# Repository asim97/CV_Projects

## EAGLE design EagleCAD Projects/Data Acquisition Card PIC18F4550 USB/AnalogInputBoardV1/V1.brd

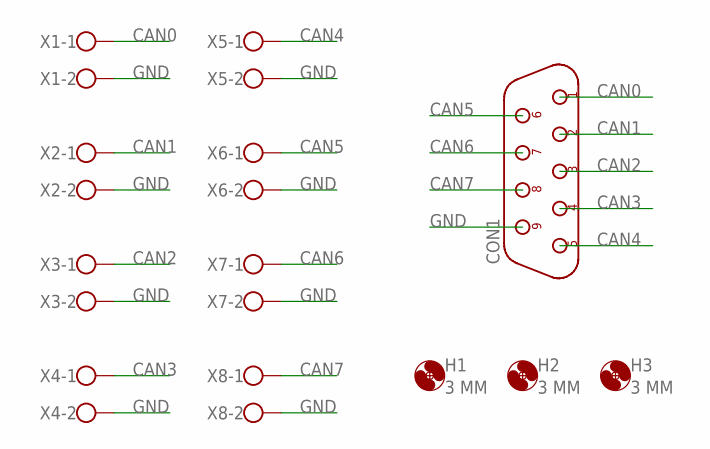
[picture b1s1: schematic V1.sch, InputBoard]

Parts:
CON1: DB9F/90; D-09F/90
H1, H2, H3: 3 MM; 3,0
X1, X2, X3, X4, X5, X6, X7, X8: W237-102

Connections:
CAN0: CON1.1, X1.1
CAN1: CON1.2, X2.1
CAN2: CON1.3, X3.1
CAN3: CON1.4, X4.1
CAN4: CON1.5, X5.1
CAN5: CON1.6, X6.1
CAN6: CON1.7, X7.1
CAN7: CON1.8, X8.1
GND: CON1.9, X1.2, X2.2, X3.2, X4.2, X5.2, X6.2, X7.2, X8.2

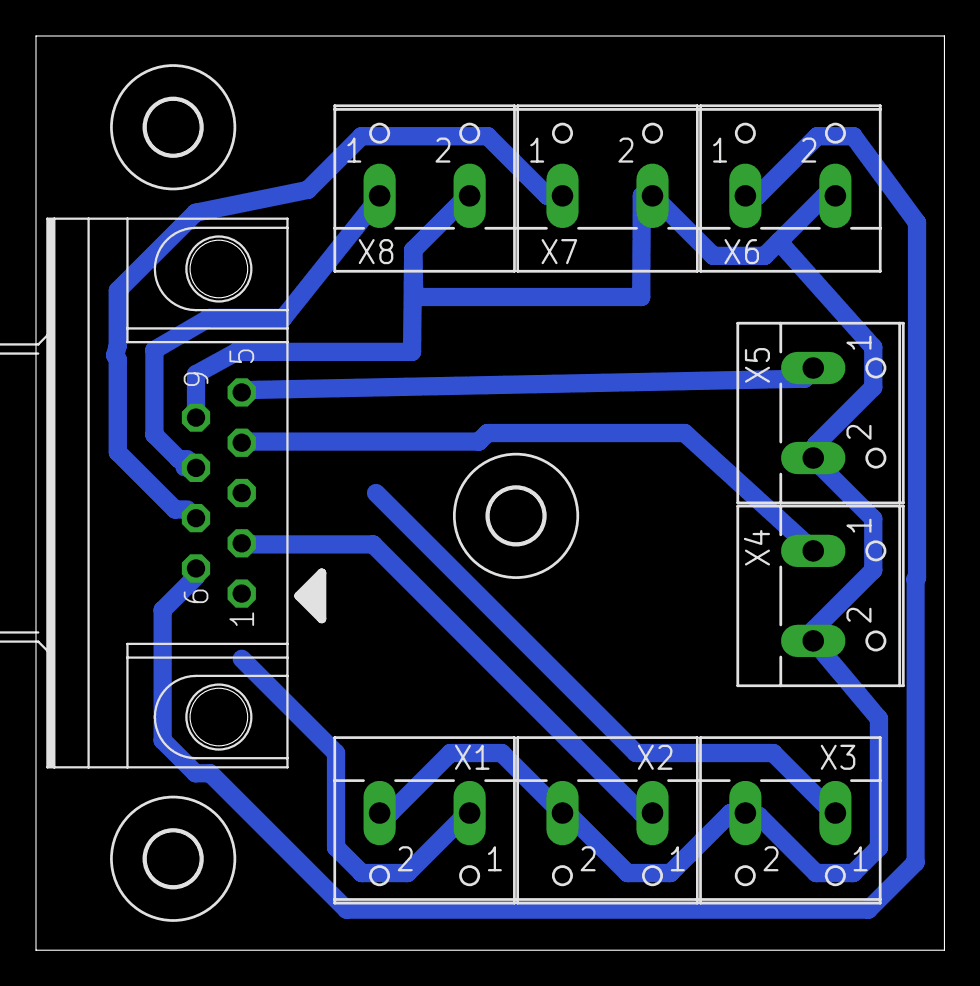
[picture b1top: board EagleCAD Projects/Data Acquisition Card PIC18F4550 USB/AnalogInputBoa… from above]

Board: 2 copper layers, 50.5 x 50.8 mm, 12 parts (0 on the bottom side), 9 nets.

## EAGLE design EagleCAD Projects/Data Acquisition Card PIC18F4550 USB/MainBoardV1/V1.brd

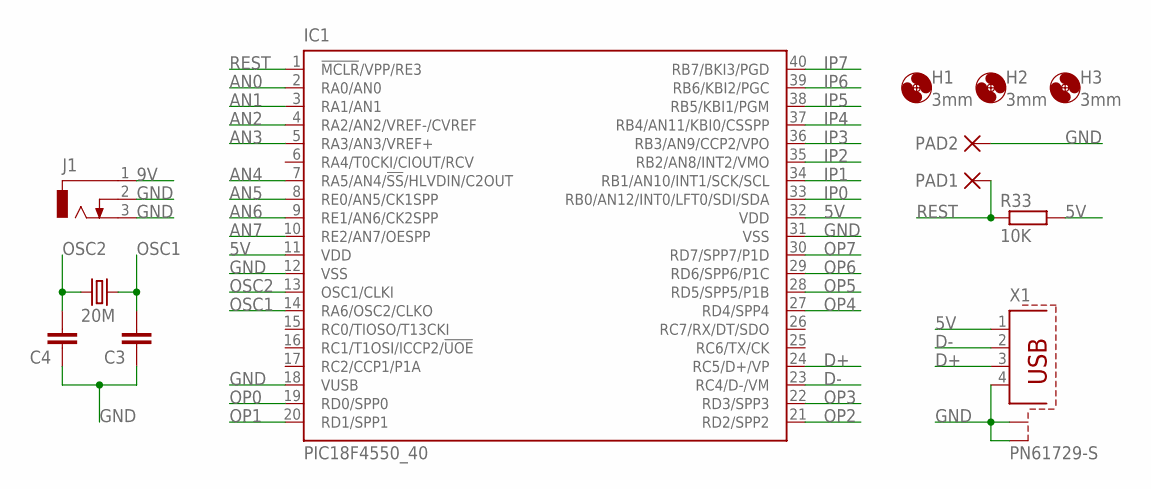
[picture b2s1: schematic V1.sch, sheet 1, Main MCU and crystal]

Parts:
20M: CRYSTALHC18U-V; HC18U-V
C3, C4: C5/2.5; C5B2.5
H1, H2, H3: 3mm; 3,0
IC1: PIC18F4550_40; DIL40
J1: DCJ0303
PAD1, PAD2: PAD-0320; 0320
R33: 10K; 0207/10
X1: PN61729-S

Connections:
5V: IC1.11 (VDD), IC1.32 (VDD), R33.2, X1.1; also elsewhere on the board
9V: J1.1; also elsewhere on the board
AN0: IC1.2 (RA0/AN0); also elsewhere on the board
AN1: IC1.3 (RA1/AN1); also elsewhere on the board
AN2: IC1.4 (RA2/AN2/VREF-/CVREF); also elsewhere on the board
AN3: IC1.5 (RA3/AN3/VREF+); also elsewhere on the board
AN4: IC1.7 (RA5/AN4/!SS!/HLVDIN/C2OUT); also elsewhere on the board
AN5: IC1.8 (RE0/AN5/CK1SPP); also elsewhere on the board
AN6: IC1.9 (RE1/AN6/CK2SPP); also elsewhere on the board
AN7: IC1.10 (RE2/AN7/OESPP); also elsewhere on the board
D+: IC1.24 (RC5/D+/VP), X1.3
D-: IC1.23 (RC4/D-/VM), X1.2
GND: C3.1, C4.1, IC1.12 (VSS), IC1.18 (VUSB), IC1.31 (VSS), J1.2, J1.3, PAD2.P$1, X1.4, X1.S1, X1.S2; also elsewhere on the board
IP0: IC1.33 (RB0/AN12/INT0/LFT0/SDI/SDA); also elsewhere on the board
IP1: IC1.34 (RB1/AN10/INT1/SCK/SCL); also elsewhere on the board
IP2: IC1.35 (RB2/AN8/INT2/VMO); also elsewhere on the board
IP3: IC1.36 (RB3/AN9/CCP2/VPO); also elsewhere on the board
IP4: IC1.37 (RB4/AN11/KBI0/CSSPP); also elsewhere on the board
IP5: IC1.38 (RB5/KBI1/PGM); also elsewhere on the board
IP6: IC1.39 (RB6/KBI2/PGC); also elsewhere on the board
IP7: IC1.40 (RB7/BKI3/PGD); also elsewhere on the board
OP0: IC1.19 (RD0/SPP0); also elsewhere on the board
OP1: IC1.20 (RD1/SPP1); also elsewhere on the board
OP2: IC1.21 (RD2/SPP2); also elsewhere on the board
OP3: IC1.22 (RD3/SPP3); also elsewhere on the board
OP4: IC1.27 (RD4/SPP4); also elsewhere on the board
OP5: IC1.28 (RD5/SPP5/P1B); also elsewhere on the board
OP6: IC1.29 (RD6/SPP6/P1C); also elsewhere on the board
OP7: IC1.30 (RD7/SPP7/P1D); also elsewhere on the board
OSC1: 20M.2, C3.2, IC1.14 (RA6/OSC2/CLKO)
OSC2: 20M.1, C4.2, IC1.13 (OSC1/CLKI)
REST: IC1.1 (!MCLR!/VPP/RE3), PAD1.P$1, R33.1

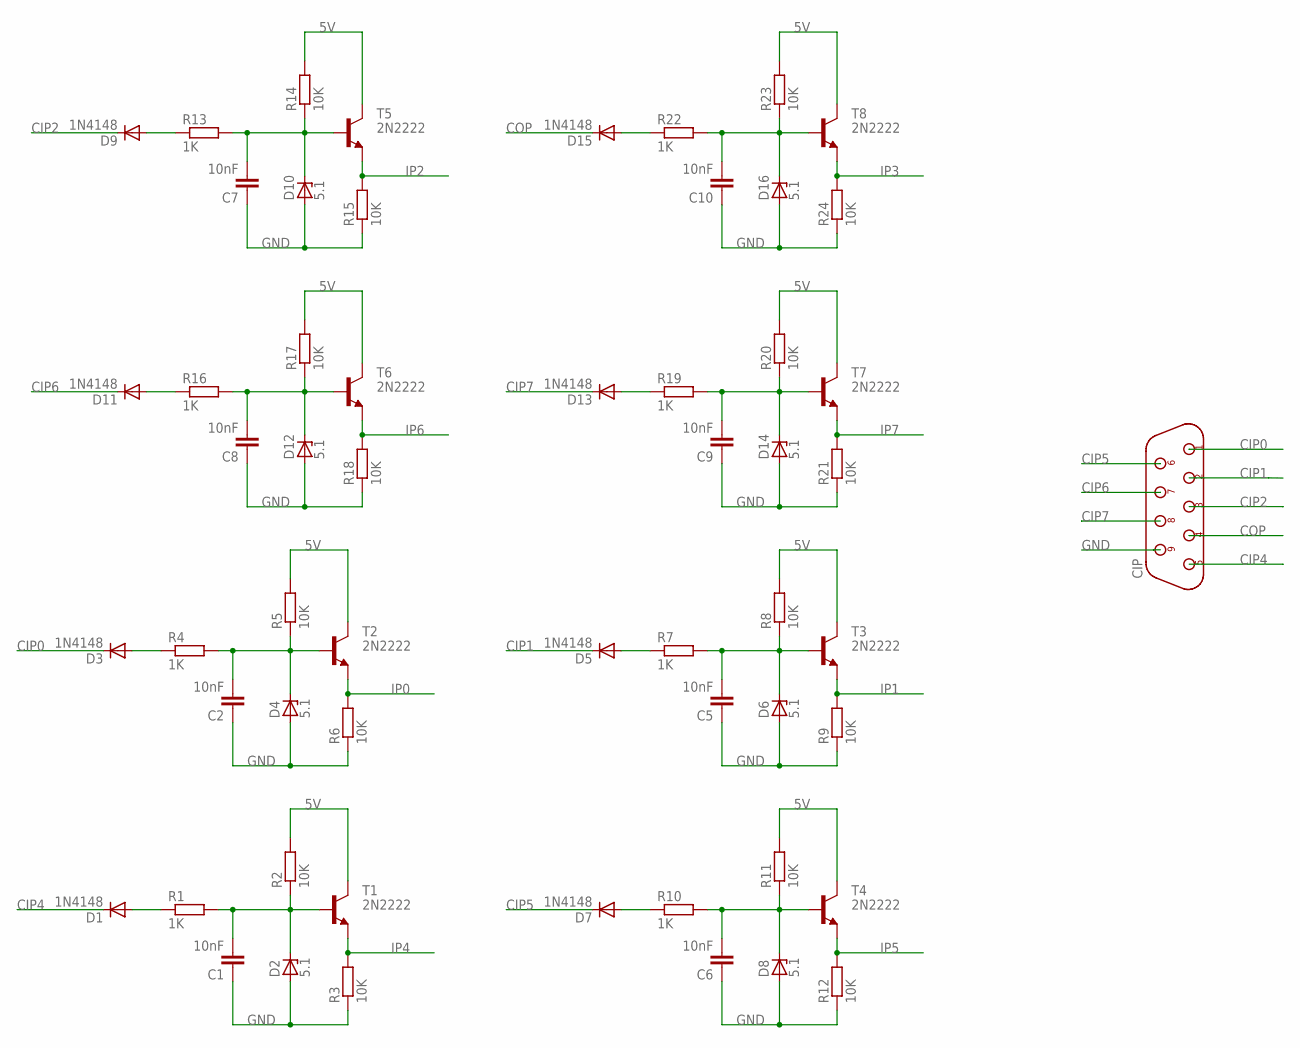
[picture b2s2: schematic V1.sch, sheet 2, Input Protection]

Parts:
C1, C2, C5, C6, C7, C8, C9, C10: 10nF; C5B2.5
CIP: DB9F/90; D-09F/90
D1, D3, D5, D7, D9, D11, D13, D15: 1N4148; DO35-10
D2, D4, D6, D8, D10, D12, D14, D16: 5.1; ZDIO-10
R1, R4, R7, R10, R13, R16, R19, R22: 1K; 0207/10
R2, R3, R5, R6, R8, R9, R11, R12, R14, R15, R17, R18, R20, R21, R23, R24: 10K; 0207/10
T1, T2, T3, T4, T5, T6, T7, T8: 2N2222; TO92-EBC-OVAL

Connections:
5V: R2.2, R5.2, R8.2, R11.2, R14.2, R17.2, R20.2, R23.2, T1.C, T2.C, T3.C, T4.C, T5.C, T6.C, T7.C, T8.C; also elsewhere on the board
CIP0: CIP.1, D3.C
CIP1: CIP.2, D5.C
CIP2: CIP.3, D9.C
CIP4: CIP.5, D1.C
CIP5: CIP.6, D7.C
CIP6: CIP.7, D11.C
CIP7: CIP.8, D13.C
COP: CIP.4, D15.C
GND: C1.1, C2.1, C5.1, C6.1, C7.1, C8.1, C9.1, C10.1, CIP.9, D2.A, D4.A, D6.A, D8.A, D10.A, D12.A, D14.A, D16.A, R3.1, R6.1, R9.1, R12.1, R15.1, R18.1, R21.1, R24.1; also elsewhere on the board
IP0: R6.2, T2.E; also elsewhere on the board
IP1: R9.2, T3.E; also elsewhere on the board
IP2: R15.2, T5.E; also elsewhere on the board
IP3: R24.2, T8.E; also elsewhere on the board
IP4: R3.2, T1.E; also elsewhere on the board
IP5: R12.2, T4.E; also elsewhere on the board
IP6: R18.2, T6.E; also elsewhere on the board
IP7: R21.2, T7.E; also elsewhere on the board
unnamed: D1.A, R1.1
unnamed: C1.2, D2.C, R1.2, R2.1, T1.B
unnamed: D3.A, R4.1
unnamed: C2.2, D4.C, R4.2, R5.1, T2.B
unnamed: D5.A, R7.1
unnamed: C5.2, D6.C, R7.2, R8.1, T3.B
unnamed: D7.A, R10.1
unnamed: C6.2, D8.C, R10.2, R11.1, T4.B
unnamed: D9.A, R13.1
unnamed: C7.2, D10.C, R13.2, R14.1, T5.B
unnamed: D11.A, R16.1
unnamed: C8.2, D12.C, R16.2, R17.1, T6.B
unnamed: D13.A, R19.1
unnamed: C9.2, D14.C, R19.2, R20.1, T7.B
unnamed: D15.A, R22.1
unnamed: C10.2, D16.C, R22.2, R23.1, T8.B

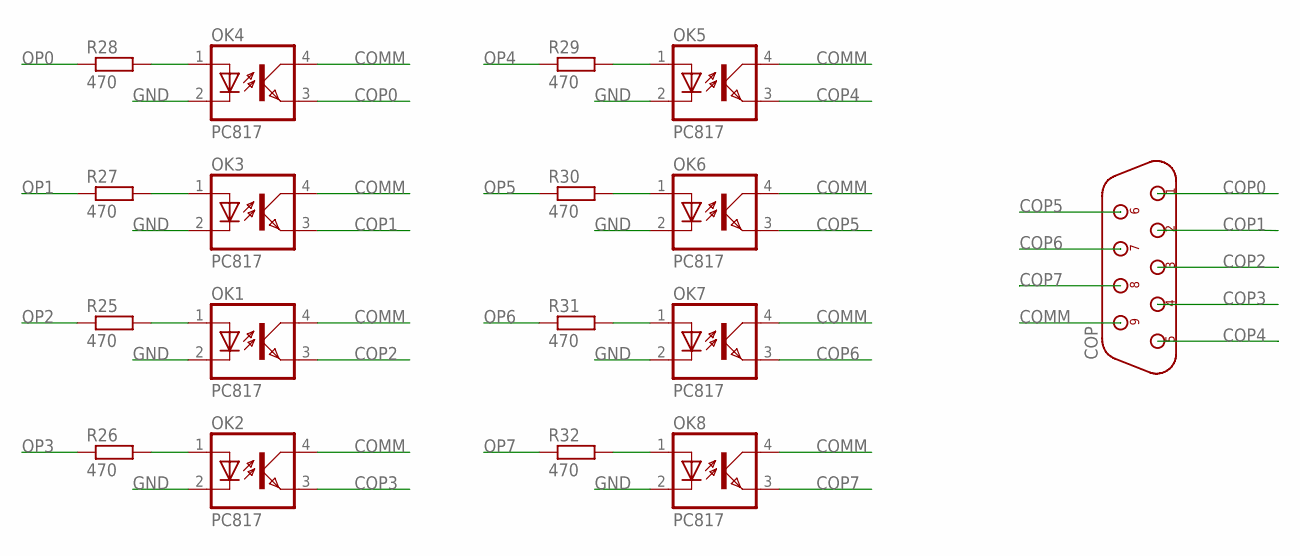
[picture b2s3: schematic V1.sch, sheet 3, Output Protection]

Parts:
COP: DB9F/90; D-09F/90
OK1, OK2, OK3, OK4, OK5, OK6, OK7, OK8: PC817; DIL04
R25, R26, R27, R28, R29, R30, R31, R32: 470; 0207/10

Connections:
COMM: COP.9, OK1.4 (COL), OK2.4 (COL), OK3.4 (COL), OK4.4 (COL), OK5.4 (COL), OK6.4 (COL), OK7.4 (COL), OK8.4 (COL)
COP0: COP.1, OK4.3 (EMIT)
COP1: COP.2, OK3.3 (EMIT)
COP2: COP.3, OK1.3 (EMIT)
COP3: COP.4, OK2.3 (EMIT)
COP4: COP.5, OK5.3 (EMIT)
COP5: COP.6, OK6.3 (EMIT)
COP6: COP.7, OK7.3 (EMIT)
COP7: COP.8, OK8.3 (EMIT)
GND: OK1.2 (C), OK2.2 (C), OK3.2 (C), OK4.2 (C), OK5.2 (C), OK6.2 (C), OK7.2 (C), OK8.2 (C); also elsewhere on the board
unnamed: OK1.1 (A), R25.2
unnamed: OK2.1 (A), R26.2
unnamed: OK3.1 (A), R27.2
unnamed: OK4.1 (A), R28.2
unnamed: OK5.1 (A), R29.2
unnamed: OK6.1 (A), R30.2
unnamed: OK7.1 (A), R31.2
unnamed: OK8.1 (A), R32.2
OP0: R28.1; also elsewhere on the board
OP1: R27.1; also elsewhere on the board
OP2: R25.1; also elsewhere on the board
OP3: R26.1; also elsewhere on the board
OP4: R29.1; also elsewhere on the board
OP5: R30.1; also elsewhere on the board
OP6: R31.1; also elsewhere on the board
OP7: R32.1; also elsewhere on the board

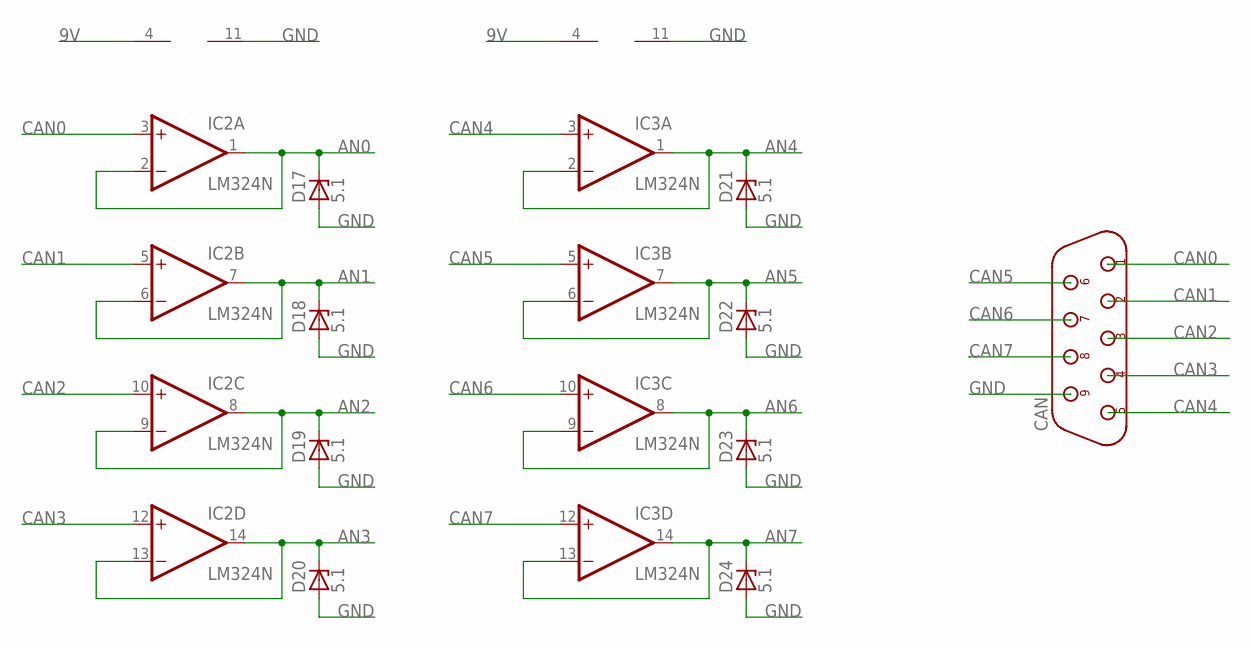
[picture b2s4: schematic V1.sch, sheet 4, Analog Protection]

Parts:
CAN: DB9F/90; D-09F/90
D17, D18, D19, D20, D21, D22, D23, D24: 5.1; ZDIO-10
IC2, IC3: LM324N; DIL14

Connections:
9V: IC2.4 (V+), IC3.4 (V+); also elsewhere on the board
AN0: D17.C, IC2.1 (OUT), IC2.2 (-IN); also elsewhere on the board
AN1: D18.C, IC2.6 (-IN), IC2.7 (OUT); also elsewhere on the board
AN2: D19.C, IC2.8 (OUT), IC2.9 (-IN); also elsewhere on the board
AN3: D20.C, IC2.13 (-IN), IC2.14 (OUT); also elsewhere on the board
AN4: D21.C, IC3.1 (OUT), IC3.2 (-IN); also elsewhere on the board
AN5: D22.C, IC3.6 (-IN), IC3.7 (OUT); also elsewhere on the board
AN6: D23.C, IC3.8 (OUT), IC3.9 (-IN); also elsewhere on the board
AN7: D24.C, IC3.13 (-IN), IC3.14 (OUT); also elsewhere on the board
CAN0: CAN.1, IC2.3 (+IN)
CAN1: CAN.2, IC2.5 (+IN)
CAN2: CAN.3, IC2.10 (+IN)
CAN3: CAN.4, IC2.12 (+IN)
CAN4: CAN.5, IC3.3 (+IN)
CAN5: CAN.6, IC3.5 (+IN)
CAN6: CAN.7, IC3.10 (+IN)
CAN7: CAN.8, IC3.12 (+IN)
GND: CAN.9, D17.A, D18.A, D19.A, D20.A, D21.A, D22.A, D23.A, D24.A, IC2.11 (V-), IC3.11 (V-); also elsewhere on the board

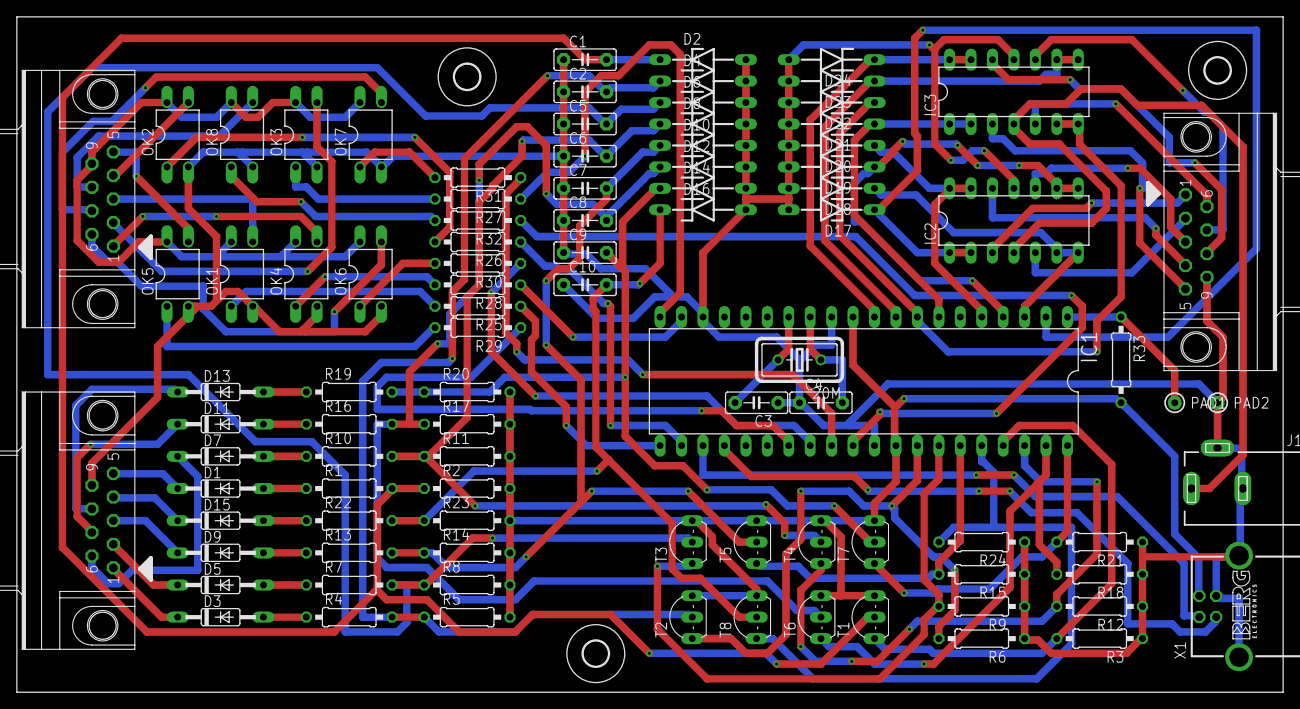
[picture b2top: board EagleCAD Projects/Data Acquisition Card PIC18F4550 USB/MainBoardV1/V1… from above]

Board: 2 copper layers, 150.0 x 80.0 mm, 97 parts (0 on the bottom side), 81 nets.

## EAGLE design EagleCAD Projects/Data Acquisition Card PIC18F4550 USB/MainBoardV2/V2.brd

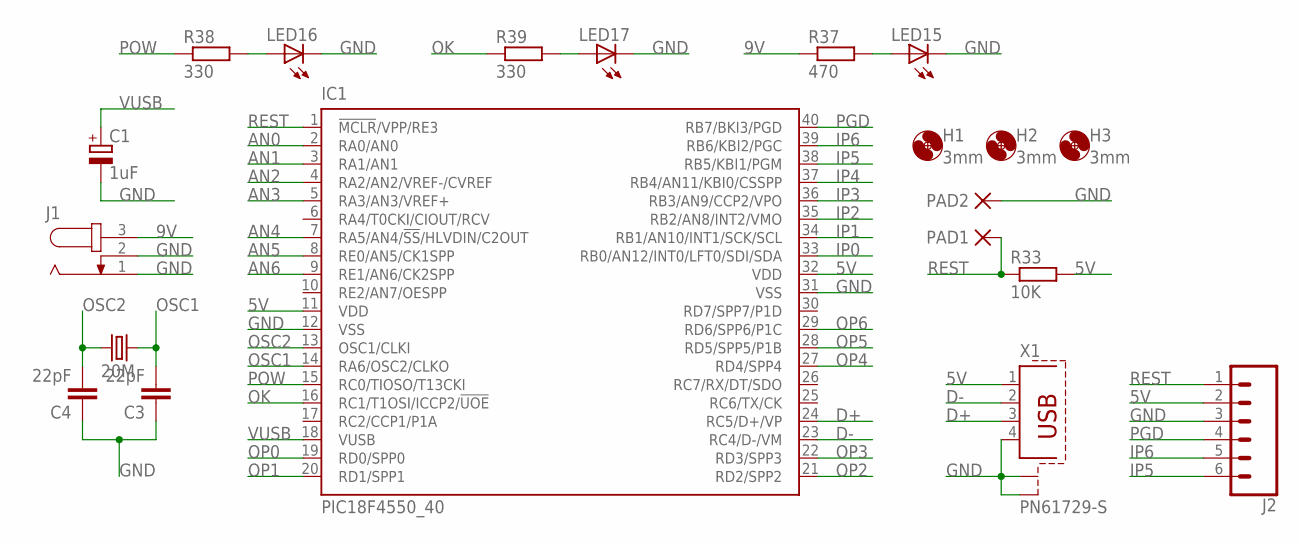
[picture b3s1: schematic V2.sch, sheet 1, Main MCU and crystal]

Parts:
20M: CRYSTALHC18U-V; HC18U-V
C1: 1uF; E2-5
C3, C4: 22pF; C5B2.5
H1, H2, H3: 3mm; 3,0
IC1: PIC18F4550_40; DIL40
J1: JACK-PLUG0; SPC4077
J2: CONN_06LONGPADS; 1X06_LONGPADS
LED15, LED16, LED17: LED5MM
PAD1, PAD2: PAD-0320; 0320
R33: 10K; 0207/10
R37: 470; 0207/10
R38, R39: 330; 0207/10
X1: PN61729-S

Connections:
5V: IC1.11 (VDD), IC1.32 (VDD), J2.2, R33.2, X1.1; also elsewhere on the board
9V: J1.3, R37.1; also elsewhere on the board
AN0: IC1.2 (RA0/AN0); also elsewhere on the board
AN1: IC1.3 (RA1/AN1); also elsewhere on the board
AN2: IC1.4 (RA2/AN2/VREF-/CVREF); also elsewhere on the board
AN3: IC1.5 (RA3/AN3/VREF+); also elsewhere on the board
AN4: IC1.7 (RA5/AN4/!SS!/HLVDIN/C2OUT); also elsewhere on the board
AN5: IC1.8 (RE0/AN5/CK1SPP); also elsewhere on the board
AN6: IC1.9 (RE1/AN6/CK2SPP); also elsewhere on the board
D+: IC1.24 (RC5/D+/VP), X1.3
D-: IC1.23 (RC4/D-/VM), X1.2
GND: C1.-, C3.1, C4.1, IC1.12 (VSS), IC1.31 (VSS), J1.1, J1.2, J2.3, LED15.K (C), LED16.K (C), LED17.K (C), PAD2.P$1, X1.4, X1.S1, X1.S2; also elsewhere on the board
IP0: IC1.33 (RB0/AN12/INT0/LFT0/SDI/SDA); also elsewhere on the board
IP1: IC1.34 (RB1/AN10/INT1/SCK/SCL); also elsewhere on the board
IP2: IC1.35 (RB2/AN8/INT2/VMO); also elsewhere on the board
IP3: IC1.36 (RB3/AN9/CCP2/VPO); also elsewhere on the board
IP4: IC1.37 (RB4/AN11/KBI0/CSSPP); also elsewhere on the board
IP5: IC1.38 (RB5/KBI1/PGM), J2.6; also elsewhere on the board
IP6: IC1.39 (RB6/KBI2/PGC), J2.5; also elsewhere on the board
unnamed: LED15.A, R37.2
unnamed: LED16.A, R38.2
unnamed: LED17.A, R39.2
OK: IC1.16 (RC1/T1OSI/ICCP2/!UOE), R39.1
OP0: IC1.19 (RD0/SPP0); also elsewhere on the board
OP1: IC1.20 (RD1/SPP1); also elsewhere on the board
OP2: IC1.21 (RD2/SPP2); also elsewhere on the board
OP3: IC1.22 (RD3/SPP3); also elsewhere on the board
OP4: IC1.27 (RD4/SPP4); also elsewhere on the board
OP5: IC1.28 (RD5/SPP5/P1B); also elsewhere on the board
OP6: IC1.29 (RD6/SPP6/P1C); also elsewhere on the board
OSC1: 20M.2, C3.2, IC1.14 (RA6/OSC2/CLKO)
OSC2: 20M.1, C4.2, IC1.13 (OSC1/CLKI)
PGD: IC1.40 (RB7/BKI3/PGD), J2.4
POW: IC1.15 (RC0/TIOSO/T13CKI), R38.1
REST: IC1.1 (!MCLR!/VPP/RE3), J2.1, PAD1.P$1, R33.1
VUSB: C1.+, IC1.18 (VUSB)

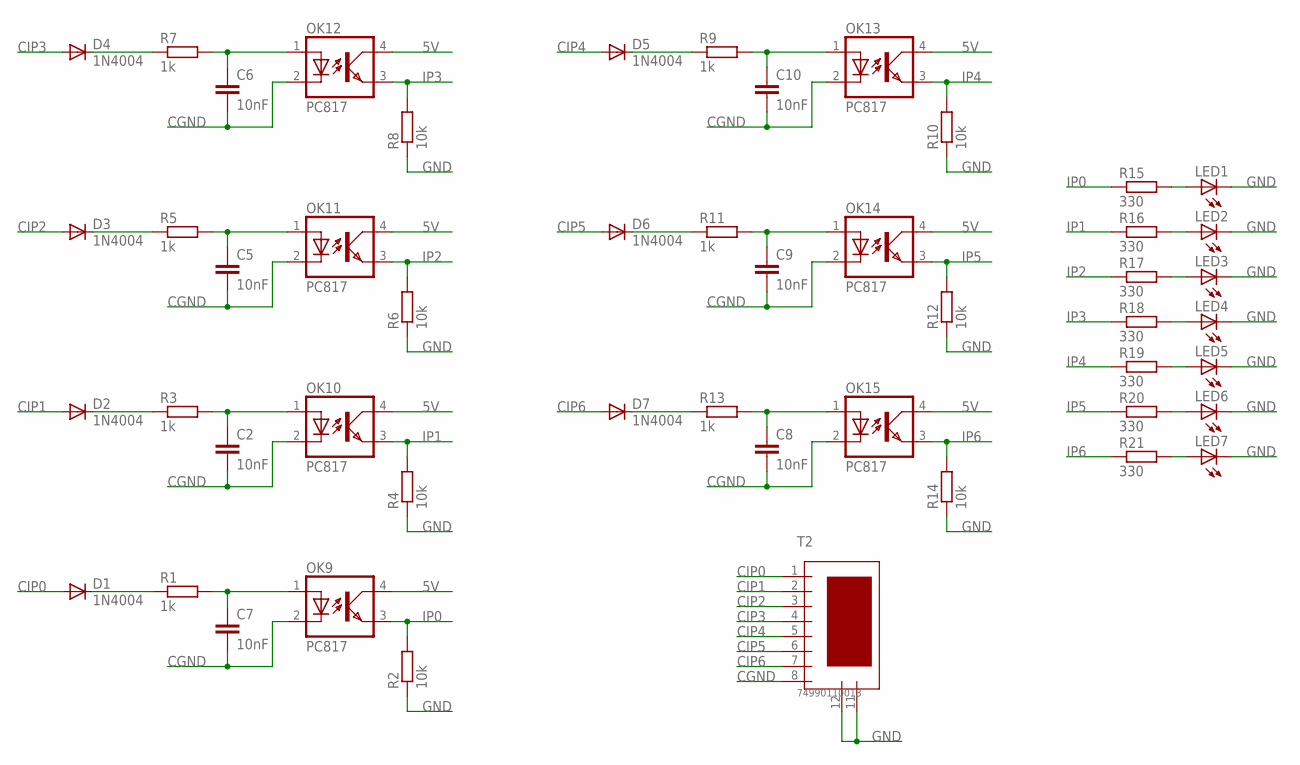
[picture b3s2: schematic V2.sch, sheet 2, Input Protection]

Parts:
C2, C5, C6, C7, C8, C9, C10: 10nF; C5B2.5
D1, D2, D3, D4, D5, D6, D7: 1N4004; DO41-10
LED1, LED2, LED3, LED4, LED5, LED6, LED7: LED5MM
OK9, OK10, OK11, OK12, OK13, OK14, OK15: PC817; DIL04
R1, R3, R5, R7, R9, R11, R13: 1k; 0207/10
R2, R4, R6, R8, R10, R12, R14: 10k; 0207/10
R15, R16, R17, R18, R19, R20, R21: 330; 0207/10
T2: 74990110013; 01LAN_RJ45_10/00_STD

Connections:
5V: OK9.4 (COL), OK10.4 (COL), OK11.4 (COL), OK12.4 (COL), OK13.4 (COL), OK14.4 (COL), OK15.4 (COL); also elsewhere on the board
CGND: C2.2, C5.2, C6.2, C7.2, C8.2, C9.2, C10.2, OK9.2 (C), OK10.2 (C), OK11.2 (C), OK12.2 (C), OK13.2 (C), OK14.2 (C), OK15.2 (C), T2.8 (7)
CIP0: D1.A, T2.1
CIP1: D2.A, T2.2
CIP2: D3.A, T2.3
CIP3: D4.A, T2.4
CIP4: D5.A, T2.5
CIP5: D6.A, T2.6
CIP6: D7.A, T2.7 (8)
GND: LED1.K (C), LED2.K (C), LED3.K (C), LED4.K (C), LED5.K (C), LED6.K (C), LED7.K (C), R2.1, R4.1, R6.1, R8.1, R10.1, R12.1, R14.1, T2.11 (9), T2.12 (10); also elsewhere on the board
IP0: OK9.3 (EMIT), R2.2, R15.1; also elsewhere on the board
IP1: OK10.3 (EMIT), R4.2, R16.1; also elsewhere on the board
IP2: OK11.3 (EMIT), R6.2, R17.1; also elsewhere on the board
IP3: OK12.3 (EMIT), R8.2, R18.1; also elsewhere on the board
IP4: OK13.3 (EMIT), R10.2, R19.1; also elsewhere on the board
IP5: OK14.3 (EMIT), R12.2, R20.1; also elsewhere on the board
IP6: OK15.3 (EMIT), R14.2, R21.1; also elsewhere on the board
unnamed: D1.C, R1.1
unnamed: C7.1, OK9.1 (A), R1.2
unnamed: D2.C, R3.1
unnamed: C2.1, OK10.1 (A), R3.2
unnamed: D3.C, R5.1
unnamed: C5.1, OK11.1 (A), R5.2
unnamed: D4.C, R7.1
unnamed: C6.1, OK12.1 (A), R7.2
unnamed: D5.C, R9.1
unnamed: C10.1, OK13.1 (A), R9.2
unnamed: D6.C, R11.1
unnamed: C9.1, OK14.1 (A), R11.2
unnamed: D7.C, R13.1
unnamed: C8.1, OK15.1 (A), R13.2
unnamed: LED1.A, R15.2
unnamed: LED2.A, R16.2
unnamed: LED3.A, R17.2
unnamed: LED4.A, R18.2
unnamed: LED5.A, R19.2
unnamed: LED6.A, R20.2
unnamed: LED7.A, R21.2

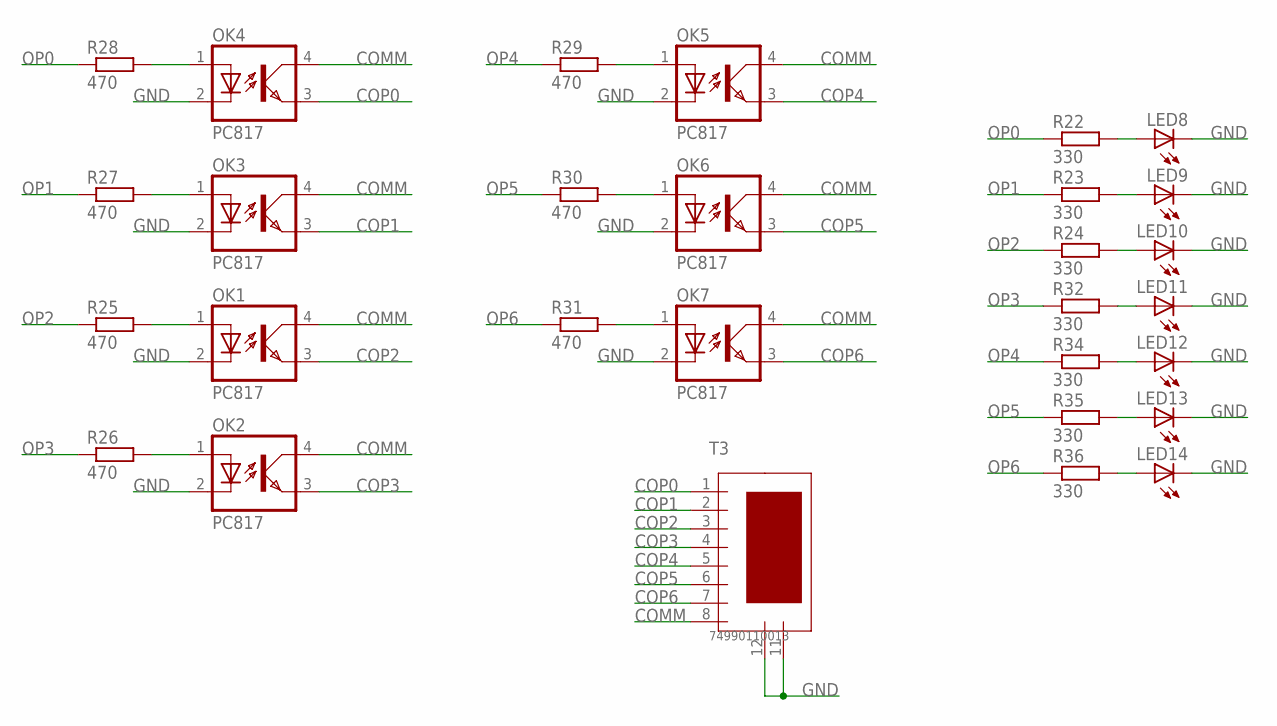
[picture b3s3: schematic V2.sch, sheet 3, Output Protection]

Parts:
LED8, LED9, LED10, LED11, LED12, LED13, LED14: LED5MM
OK1, OK2, OK3, OK4, OK5, OK6, OK7: PC817; DIL04
R22, R23, R24, R32, R34, R35, R36: 330; 0207/10
R25, R26, R27, R28, R29, R30, R31: 470; 0207/10
T3: 74990110013; 01LAN_RJ45_10/00_STD

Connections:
COMM: OK1.4 (COL), OK2.4 (COL), OK3.4 (COL), OK4.4 (COL), OK5.4 (COL), OK6.4 (COL), OK7.4 (COL), T3.8 (7)
COP0: OK4.3 (EMIT), T3.1
COP1: OK3.3 (EMIT), T3.2
COP2: OK1.3 (EMIT), T3.3
COP3: OK2.3 (EMIT), T3.4
COP4: OK5.3 (EMIT), T3.5
COP5: OK6.3 (EMIT), T3.6
COP6: OK7.3 (EMIT), T3.7 (8)
GND: LED8.K (C), LED9.K (C), LED10.K (C), LED11.K (C), LED12.K (C), LED13.K (C), LED14.K (C), OK1.2 (C), OK2.2 (C), OK3.2 (C), OK4.2 (C), OK5.2 (C), OK6.2 (C), OK7.2 (C), T3.11 (9), T3.12 (10); also elsewhere on the board
unnamed: OK1.1 (A), R25.2
unnamed: OK2.1 (A), R26.2
unnamed: OK3.1 (A), R27.2
unnamed: OK4.1 (A), R28.2
unnamed: LED8.A, R22.2
unnamed: OK5.1 (A), R29.2
unnamed: LED9.A, R23.2
unnamed: LED10.A, R24.2
unnamed: LED11.A, R32.2
unnamed: LED12.A, R34.2
unnamed: OK6.1 (A), R30.2
unnamed: LED13.A, R35.2
unnamed: LED14.A, R36.2
unnamed: OK7.1 (A), R31.2
OP0: R22.1, R28.1; also elsewhere on the board
OP1: R23.1, R27.1; also elsewhere on the board
OP2: R24.1, R25.1; also elsewhere on the board
OP3: R26.1, R32.1; also elsewhere on the board
OP4: R29.1, R34.1; also elsewhere on the board
OP5: R30.1, R35.1; also elsewhere on the board
OP6: R31.1, R36.1; also elsewhere on the board

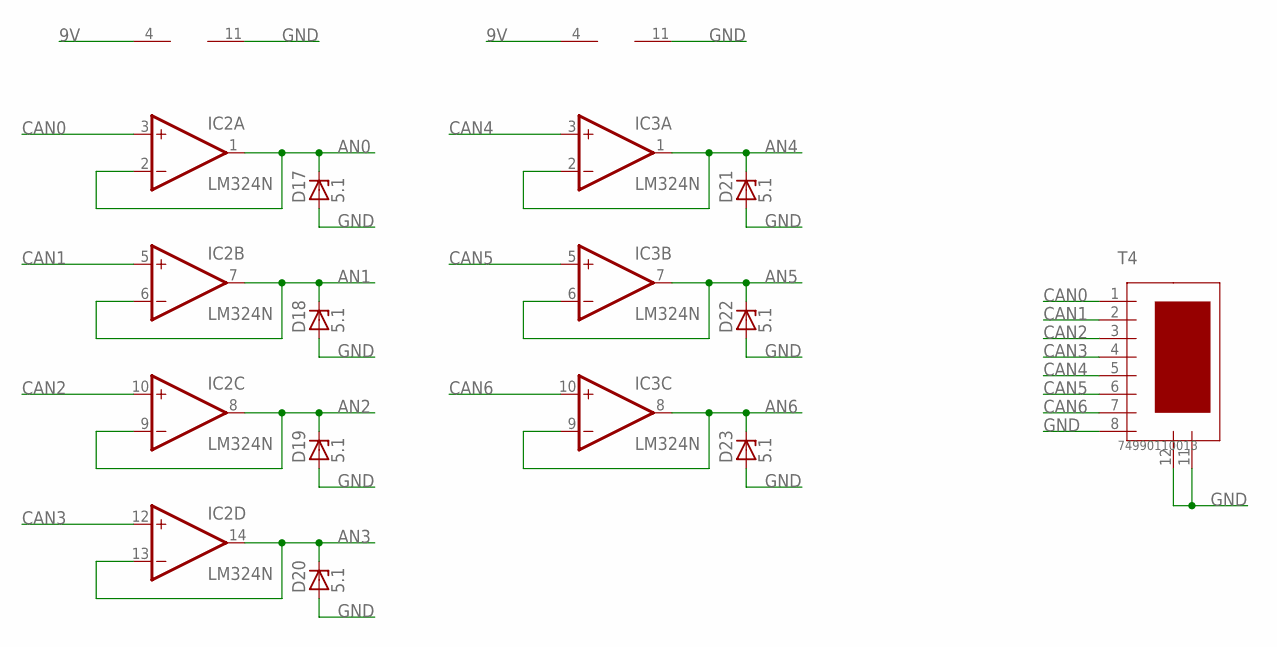
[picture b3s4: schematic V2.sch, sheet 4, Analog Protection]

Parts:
D17, D18, D19, D20, D21, D22, D23: 5.1; ZDIO-10
IC2, IC3: LM324N; DIL14
T4: 74990110013; 01LAN_RJ45_10/00_STD

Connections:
9V: IC2.4 (V+), IC3.4 (V+); also elsewhere on the board
AN0: D17.C, IC2.1 (OUT), IC2.2 (-IN); also elsewhere on the board
AN1: D18.C, IC2.6 (-IN), IC2.7 (OUT); also elsewhere on the board
AN2: D19.C, IC2.8 (OUT), IC2.9 (-IN); also elsewhere on the board
AN3: D20.C, IC2.13 (-IN), IC2.14 (OUT); also elsewhere on the board
AN4: D21.C, IC3.1 (OUT), IC3.2 (-IN); also elsewhere on the board
AN5: D22.C, IC3.6 (-IN), IC3.7 (OUT); also elsewhere on the board
AN6: D23.C, IC3.8 (OUT), IC3.9 (-IN); also elsewhere on the board
CAN0: IC2.3 (+IN), T4.1
CAN1: IC2.5 (+IN), T4.2
CAN2: IC2.10 (+IN), T4.3
CAN3: IC2.12 (+IN), T4.4
CAN4: IC3.3 (+IN), T4.5
CAN5: IC3.5 (+IN), T4.6
CAN6: IC3.10 (+IN), T4.7 (8)
GND: D17.A, D18.A, D19.A, D20.A, D21.A, D22.A, D23.A, IC2.11 (V-), IC3.11 (V-), T4.8 (7), T4.11 (9), T4.12 (10); also elsewhere on the board

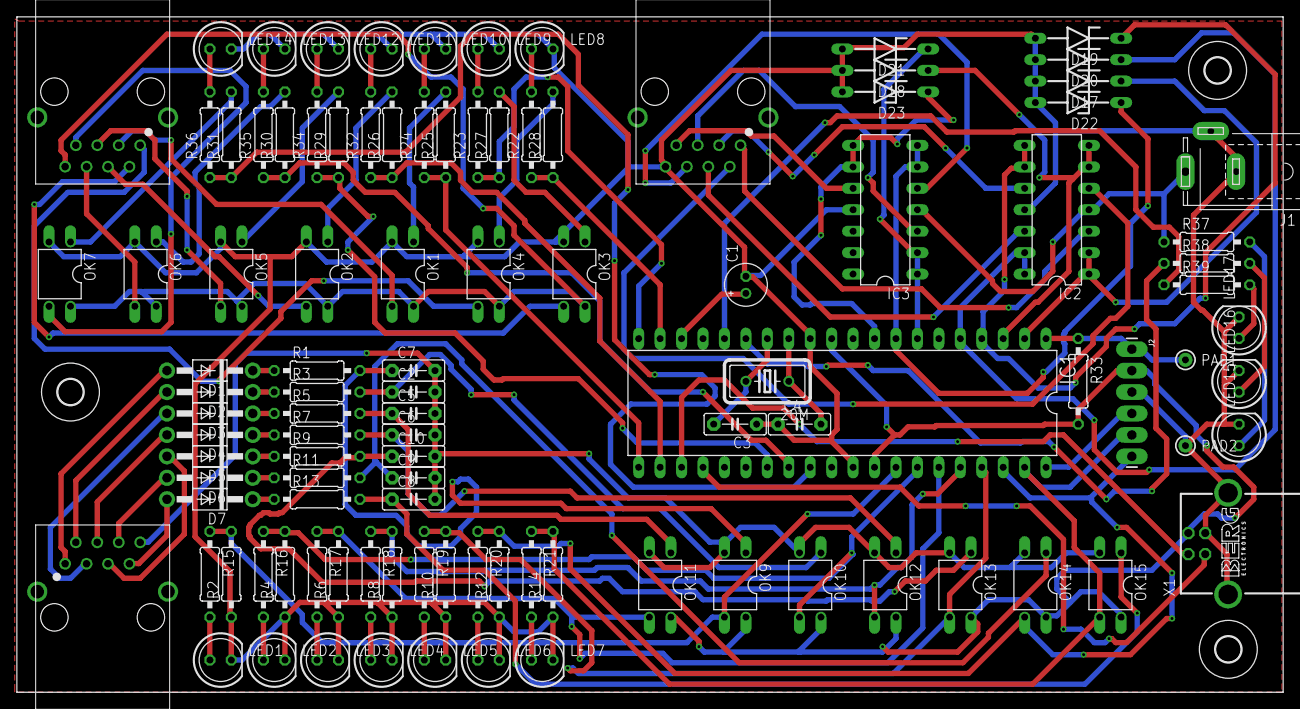
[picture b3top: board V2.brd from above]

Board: 2 copper layers, 150.0 x 80.0 mm, 109 parts (0 on the bottom side), 94 nets.

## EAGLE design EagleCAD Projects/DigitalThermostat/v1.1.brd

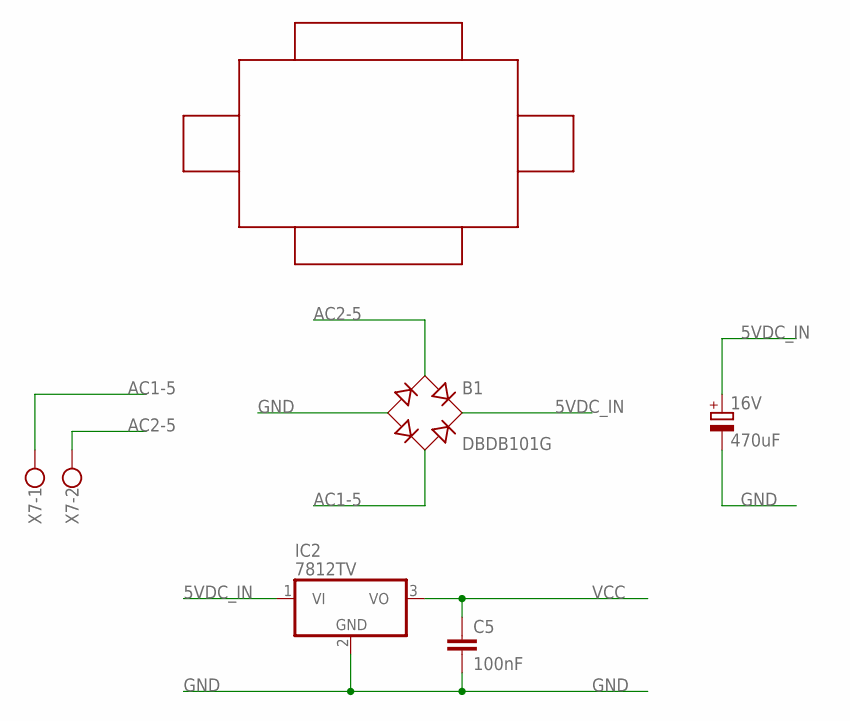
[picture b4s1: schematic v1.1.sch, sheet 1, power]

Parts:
16V: 470uF; E3,5-8
B1: DBDB101G; DB
C5: 100nF; C050-025X075
IC2: 7812TV; TO220V
U$1: TRANS_12V; 12V
X7: W237-102

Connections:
5VDC_IN: 16V.+, B1.+, IC2.1 (VI); also elsewhere on the board
AC1-5: B1.AC2, X7.1
AC2-5: B1.AC1, X7.2
GND: 16V.-, B1.-, C5.2, IC2.2 (GND); also elsewhere on the board
VCC: C5.1, IC2.3 (VO); also elsewhere on the board

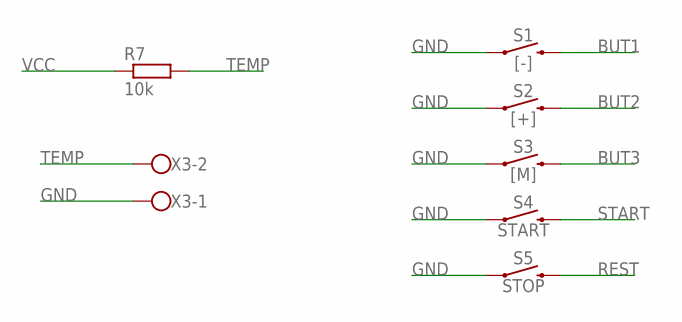
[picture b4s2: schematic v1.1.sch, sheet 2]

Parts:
R7: 10k; 0207/10
S1: [-]; TACTILE_SWITCH_PTH_6.0MM
S2: [+]; TACTILE_SWITCH_PTH_6.0MM
S3: [M]; TACTILE_SWITCH_PTH_6.0MM
S4: START; TACTILE_SWITCH_PTH_6.0MM
S5: STOP; TACTILE_SWITCH_PTH_6.0MM
X3: W237-102

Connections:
BUT1: S1.3 (2); also elsewhere on the board
BUT2: S2.3 (2); also elsewhere on the board
BUT3: S3.3 (2); also elsewhere on the board
GND: S1.1, S2.1, S3.1, S4.1, S5.1, X3.1; also elsewhere on the board
REST: S5.3 (2); also elsewhere on the board
START: S4.3 (2); also elsewhere on the board
TEMP: R7.2, X3.2; also elsewhere on the board
VCC: R7.1; also elsewhere on the board

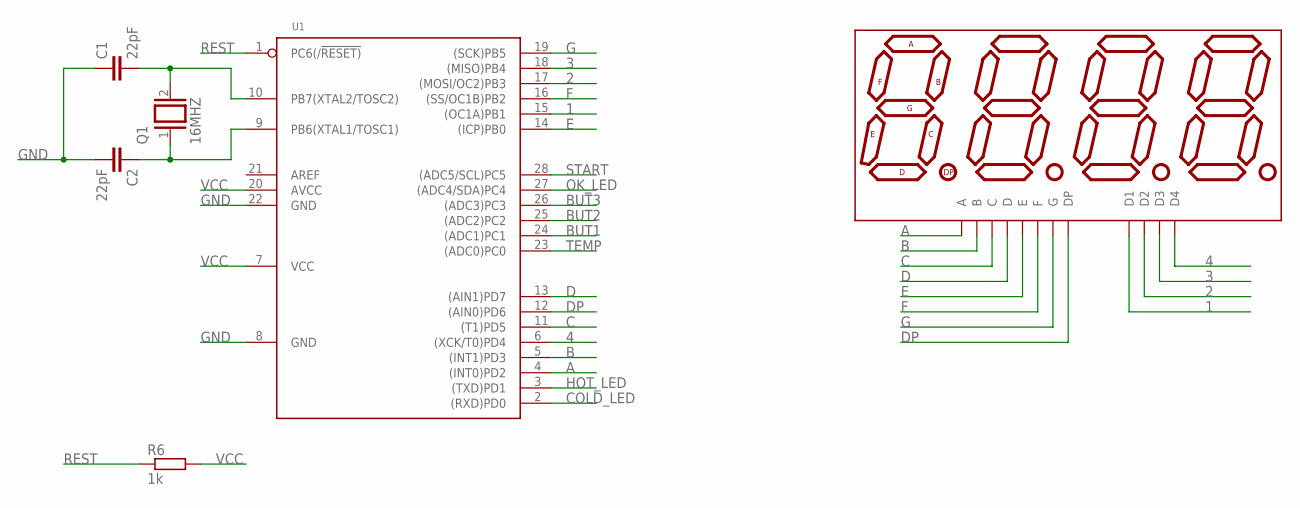
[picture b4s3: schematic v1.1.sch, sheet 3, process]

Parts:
C1, C2: 22pF; C050-025X075
DISP2: ATA8041AB; 7-SEGMENT-4DIGIT-20MM
Q1: 16MHZ; QS
R6: 1k; 0207/10
U1: MCU-ATMEGA328P-PU(DIP28); DIP28-2.54-34.7X7.62MM

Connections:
1: DISP2.12 (D1), U1.15 ((OC1A)PB1)
2: DISP2.9 (D2), U1.17 ((MOSI/OC2)PB3)
3: DISP2.8 (D3), U1.18 ((MISO)PB4)
4: DISP2.6 (D4), U1.6 ((XCK/T0)PD4)
A: DISP2.11 (A), U1.4 ((INT0)PD2)
B: DISP2.7 (B), U1.5 ((INT1)PD3)
BUT1: U1.24 ((ADC1)PC1); also elsewhere on the board
BUT2: U1.25 ((ADC2)PC2); also elsewhere on the board
BUT3: U1.26 ((ADC3)PC3); also elsewhere on the board
C: DISP2.4 (C), U1.11 ((T1)PD5)
COLD_LED: U1.2 ((RXD)PD0); also elsewhere on the board
D: DISP2.2 (D), U1.13 ((AIN1)PD7)
DP: DISP2.3 (DP), U1.12 ((AIN0)PD6)
E: DISP2.1 (E), U1.14 ((ICP)PB0)
F: DISP2.10 (F), U1.16 ((SS/OC1B)PB2)
G: DISP2.5 (G), U1.19 ((SCK)PB5)
GND: C1.1, C2.2, U1.8 (GND), U1.22 (GND); also elsewhere on the board
HOT_LED: U1.3 ((TXD)PD1); also elsewhere on the board
unnamed: C1.2, Q1.2, U1.10 (PB7(XTAL2/TOSC2))
unnamed: C2.1, Q1.1, U1.9 (PB6(XTAL1/TOSC1))
OK_LED: U1.27 ((ADC4/SDA)PC4); also elsewhere on the board
REST: R6.1, U1.1 (PC6(/!RESET)); also elsewhere on the board
START: U1.28 ((ADC5/SCL)PC5); also elsewhere on the board
TEMP: U1.23 ((ADC0)PC0); also elsewhere on the board
VCC: R6.2, U1.7 (VCC), U1.20 (AVCC); also elsewhere on the board

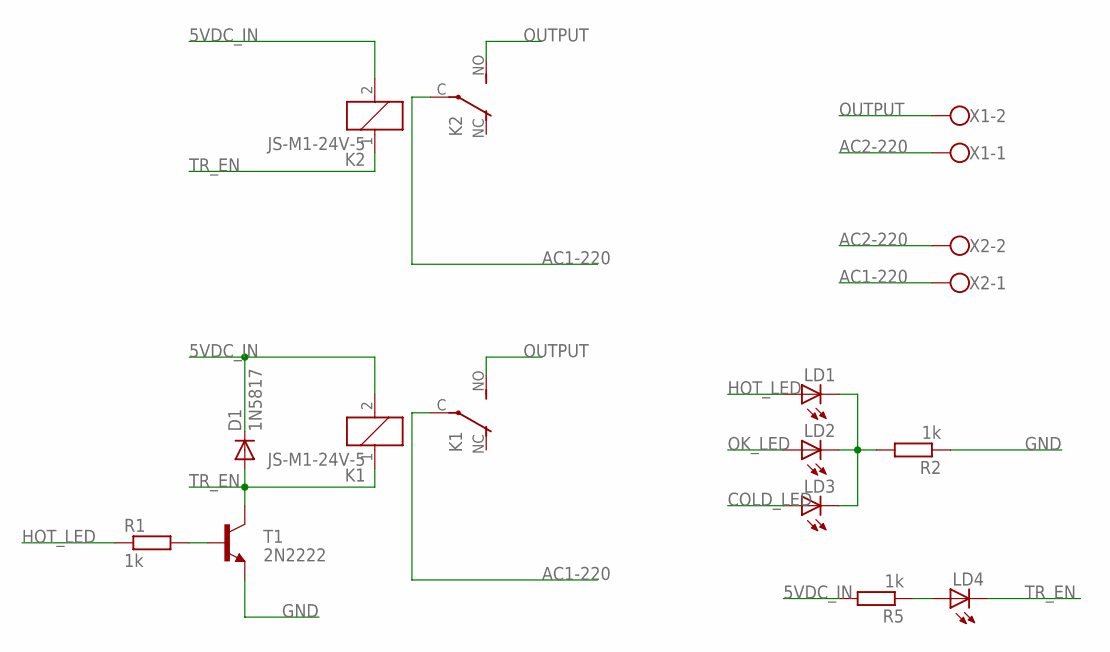
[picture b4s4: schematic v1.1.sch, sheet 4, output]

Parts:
D1: 1N5817; DO41-10
K1, K2: JS-M1-24V-5; JS-M
LD1, LD2, LD3, LD4: LED5MM
R1, R2, R5: 1k; 0207/10
T1: 2N2222; TO92-EBC-OVAL
X1, X2: W237-102

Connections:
5VDC_IN: D1.C, K1.2, K2.2, R5.2; also elsewhere on the board
AC1-220: K1.C, K2.C, X2.1
AC2-220: X1.1, X2.2
COLD_LED: LD3.A; also elsewhere on the board
GND: R2.1, T1.E; also elsewhere on the board
HOT_LED: LD1.A, R1.1; also elsewhere on the board
unnamed: LD4.A, R5.1
unnamed: LD1.K (C), LD2.K (C), LD3.K (C), R2.2
unnamed: R1.2, T1.B
OK_LED: LD2.A; also elsewhere on the board
OUTPUT: K1.NO (S), K2.NO (S), X1.2
TR_EN: D1.A, K1.1, K2.1, LD4.K (C), T1.C

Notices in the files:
parts and their libraries:
SparkFun-LED: Licensing: Creative Commons ShareAlike 4.0 International - https://creativecommons.org/licenses/by-sa/4.0
dpads: Copyright (C) 2004, Bob Starr (bobstarr@mindspring.com)
wurth_electronics_midcom_inc_v1-0: Copyright: Wurth Electronics Midcom, Inc.
